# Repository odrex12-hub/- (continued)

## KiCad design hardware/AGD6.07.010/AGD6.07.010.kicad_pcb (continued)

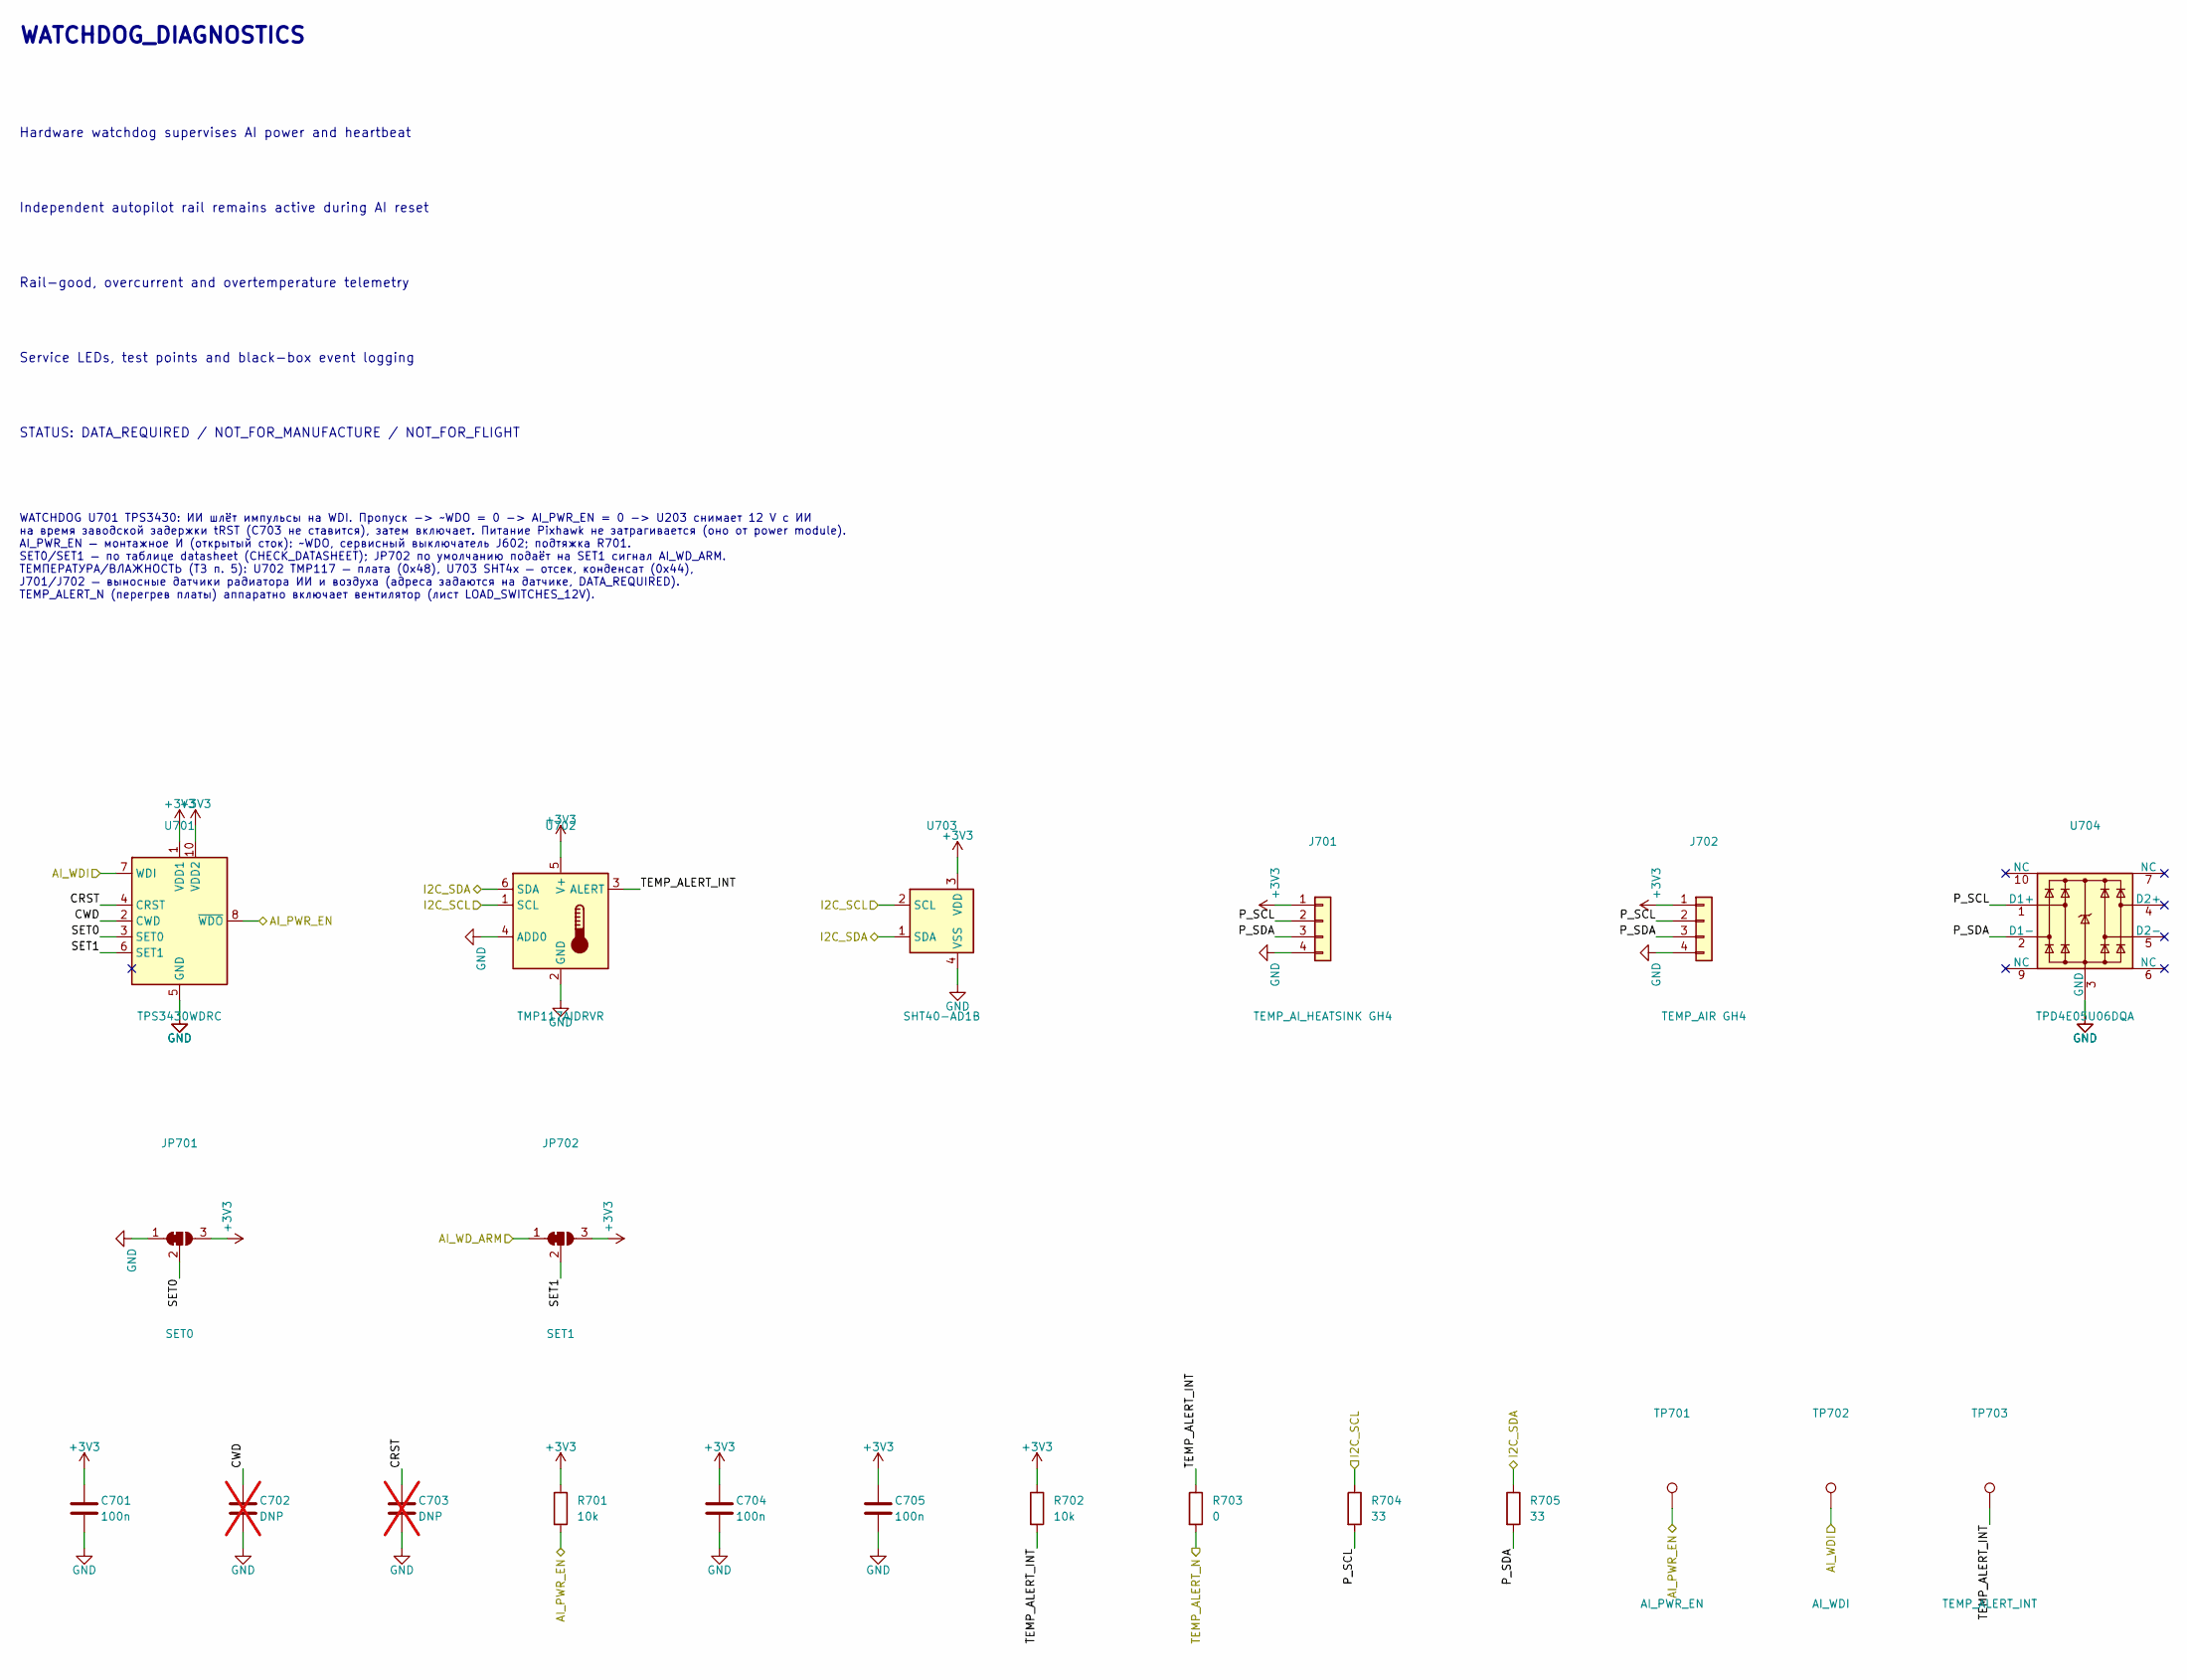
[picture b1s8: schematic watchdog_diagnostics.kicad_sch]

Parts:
C701, C704, C705: 100n; C_0402_1005Metric
C702, C703: DNP; C_0402_1005Metric; not fitted
J701: TEMP_AI_HEATSINK GH4; JST_GH_SM04B-GHS-TB_1x04-1MP_P1.25mm_Horizontal
J702: TEMP_AIR GH4; JST_GH_SM04B-GHS-TB_1x04-1MP_P1.25mm_Horizontal
JP701: SET0; SolderJumper-3_P1.3mm_Bridged12_RoundedPad1.0x1.5mm_NumberL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
JP702: SET1; SolderJumper-3_P1.3mm_Bridged12_RoundedPad1.0x1.5mm_NumberL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
R701, R702: 10k; R_0402_1005Metric
R703: 0; R_0402_1005Metric
R704, R705: 33; R_0402_1005Metric
TP701: AI_PWR_EN; TestPoint_Pad_D1.5mm
TP702: AI_WDI; TestPoint_Pad_D1.5mm
TP703: TEMP_ALERT_INT; TestPoint_Pad_D1.5mm
U701: TPS3430WDRC; VSON-10-1EP_3x3mm_P0.5mm_EP1.65x2.4mm
U702: TMP117AIDRVR; WSON-6-1EP_2x2mm_P0.65mm_EP1x1.6mm
U703: SHT40-AD1B; Sensirion_DFN-4_1.5x1.5mm_P0.8mm_SHT4x_NoCentralPad
U704: TPD4E05U06DQA; USON-10_2.5x1.0mm_P0.5mm

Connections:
+3V3: C701.1, C704.1, C705.1, J701.1, J702.1, JP701.3 (B), JP702.3 (B), R701.1, R702.1, U701.1 (VDD1), U701.10 (VDD2), U702.5 (V+), U703.3 (VDD); also elsewhere on the board
/AI_PWR_EN: R701.2, TP701.1, U701.8 (~WDO); also elsewhere on the board
/AI_WDI: TP702.1, U701.7 (WDI); also elsewhere on the board
/AI_WD_ARM: JP702.1 (A); also elsewhere on the board
/I2C_SCL: R704.1, U702.1 (SCL), U703.2 (SCL); also elsewhere on the board
/I2C_SDA: R705.1, U702.6 (SDA), U703.1 (SDA); also elsewhere on the board
/TEMP_ALERT_N: R703.2; also elsewhere on the board
/WATCHDOG_DIAGNOSTICS/CRST: C703.1, U701.4 (CRST)
/WATCHDOG_DIAGNOSTICS/CWD: C702.1, U701.2 (CWD)
/WATCHDOG_DIAGNOSTICS/P_SCL: J701.2, J702.2, R704.2, U704.1 (D1+)
/WATCHDOG_DIAGNOSTICS/P_SDA: J701.3, J702.3, R705.2, U704.2 (D1-)
/WATCHDOG_DIAGNOSTICS/SET0: JP701.2 (C), U701.3 (SET0)
/WATCHDOG_DIAGNOSTICS/SET1: JP702.2 (C), U701.6 (SET1)
/WATCHDOG_DIAGNOSTICS/TEMP_ALERT_INT: R702.2, R703.1, TP703.1, U702.3 (ALERT)
GND: C701.2, C702.2, C703.2, C704.2, C705.2, J701.4, J702.4, JP701.1 (A), U701.5 (GND), U701.11 (GND), U702.2 (GND), U702.4 (ADD0), U703.4 (VSS), U704.3 (GND), U704.8 (GND); also elsewhere on the board

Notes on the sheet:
Service LEDs, test points and black-box event logging
STATUS: DATA_REQUIRED / NOT_FOR_MANUFACTURE / NOT_FOR_FLIGHT
WATCHDOG_DIAGNOSTICS
Hardware watchdog supervises AI power and heartbeat
Rail-good, overcurrent and overtemperature telemetry
Independent autopilot rail remains active during AI reset
WATCHDOG U701 TPS3430: ИИ шлёт импульсы на WDI. Пропуск -> ~WDO = 0 -> AI_PWR_EN = 0 -> U203 снимает 12 V с ИИ на время заводской задержки tRST (C703 не ставится), затем включает. Питание Pixhawk не затрагивается (оно от power module). AI_PWR_EN — монтажное И (открытый сток): ~WDO, сервисный выключ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

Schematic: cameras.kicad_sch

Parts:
C901, C902: 10u 25V; C_1210_3225Metric
F901, F902: 1.1A; Fuse_1812_4532Metric
J901: CAM_FRONT_PWR XH2; JST_XH_B2B-XH-A_1x02_P2.50mm_Vertical
J902: CAM_DOWN_PWR XH2; JST_XH_B2B-XH-A_1x02_P2.50mm_Vertical

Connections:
+12V: F901.1, F902.1; also elsewhere on the board
/CAMERAS/V12_CAMD: C902.1, F902.2, J902.1
/CAMERAS/V12_CAMF: C901.1, F901.2, J901.1
GND: C901.2, C902.2, J901.2, J902.2; also elsewhere on the board

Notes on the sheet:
Protected power switching and synchronization trigger
CAMERAS
High-speed links routed away from switching power stages
Front navigation camera and downward observation camera
Optional depth/obstacle camera interface
DATA_REQUIRED: camera models, interface and cable type
КАМЕРЫ (ТЗ п. 4): питание 12 V через PTC. Видео: камера вперёд (SIYI A2 mini) — Ethernet через коммутатор, камера вниз — Ethernet кабелем напрямую в ИИ или в коммутатор SwitchBlox (лист ETHERNET). Синхронизация: CAM_TRIG (AUX7 Pixhawk) -> J806 на листе LOAD_SWITCHES_12V. Модели камер, объективы, ка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

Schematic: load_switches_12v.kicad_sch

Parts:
BZ801: 12V active buzzer; Buzzer_12x9.5RM7.6
C804, C811, C821, C831: 100n; C_0402_1005Metric
C805: 10u 25V; C_1210_3225Metric
D801, D802, D803, D804, D805, D808: SS14; D_SMA
D806, D809: ESD9B5.0ST5G; D_SOD-923
D807: BAT54C; SOT-23
D811, D812, D813: BAT54S; SOT-23
F801: 0.5A; Fuse_1206_3216Metric
F802: 1.5A; Fuse_1812_4532Metric
J801: VALVE1 XH2; JST_XH_B2B-XH-A_1x02_P2.50mm_Vertical
J802: VALVE2 XH2; JST_XH_B2B-XH-A_1x02_P2.50mm_Vertical
J803: LIGHTS XH2; JST_XH_B2B-XH-A_1x02_P2.50mm_Vertical
J804: FAN XH2; JST_XH_B2B-XH-A_1x02_P2.50mm_Vertical
J805: HEATER XH2; JST_XH_B2B-XH-A_1x02_P2.50mm_Vertical
J806: PUMP_PWM + CAM_TRIG GH4; JST_GH_SM04B-GHS-TB_1x04-1MP_P1.25mm_Horizontal
Q801, Q803, Q804: AO3400A; SOT-23
Q802: AO3401A; SOT-23
R804, R811, R821, R831: 4.7k; R_0402_1005Metric
R805, R842, R852, R872: 100k; R_0402_1005Metric
R806: 22k; R_0402_1005Metric
R807, R813, R823, R833: 10k; R_0402_1005Metric
R812, R822, R832: 470; R_0402_1005Metric
R841, R851, R861, R862, R871: 100; R_0402_1005Metric
TP801: ADC_RDY; TestPoint_Pad_D1.5mm
U801, U802, U803: BTS5030-1EJA; Infineon_PG-DSO-8-43
U804: ADS1115IDGSR; TSSOP-10_3x3mm_P0.5mm

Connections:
+3V3: C804.1, D811.2 (K), D812.2 (K), D813.2 (K), Q802.2 (S), R804.1, R807.1, U804.1 (ADDR), U804.8 (VDD); also elsewhere on the board
+12V: BZ801.1 (+), D808.1 (K); also elsewhere on the board
+12VA: C805.1, F801.1, F802.1, R805.1, U801.9 (VS), U802.9 (VS), U803.9 (VS); also elsewhere on the board
/BUZZER_CTL: R871.1; also elsewhere on the board
/CAM_TRIG: R862.1; also elsewhere on the board
/FAN_CTL: R841.1; also elsewhere on the board
/HEATER_CTL: R851.1; also elsewhere on the board
/I2C_SCL: U804.10 (SCL); also elsewhere on the board
/I2C_SDA: U804.9 (SDA); also elsewhere on the board
/LIGHTS_CTL: R831.1; also elsewhere on the board
/LOAD_SWITCHES_12V/ADC_RDY: R807.2, TP801.1, U804.2 (ALERT/RDY)
/LOAD_SWITCHES_12V/ALERT_DRV: D807.2, Q802.3 (D)
/LOAD_SWITCHES_12V/BUZ_G: Q804.1 (G), R871.2, R872.1
/LOAD_SWITCHES_12V/BUZ_N: BZ801.2 (-), D808.2 (A), Q804.3 (D)
/LOAD_SWITCHES_12V/DEN: R804.2, U801.3 (DEN), U802.3 (DEN), U803.3 (DEN)
/LOAD_SWITCHES_12V/FAN_CTL_R: D807.1, R841.2
/LOAD_SWITCHES_12V/FAN_G: D807.3, Q801.1 (G), R842.1
/LOAD_SWITCHES_12V/FAN_N: D804.2 (A), J804.2, Q801.3 (D)
/LOAD_SWITCHES_12V/HEAT_G: Q803.1 (G), R851.2, R852.1
/LOAD_SWITCHES_12V/HEAT_N: D805.2 (A), J805.2, Q803.3 (D)
/LOAD_SWITCHES_12V/IN1: R811.2, U801.2 (IN)
/LOAD_SWITCHES_12V/IN2: R821.2, U802.2 (IN)
/LOAD_SWITCHES_12V/IN3: R831.2, U803.2 (IN)
/LOAD_SWITCHES_12V/IS1: R812.1, R813.1, U801.4 (IS)
/LOAD_SWITCHES_12V/IS1_F: C811.1, D811.3 (COM), R813.2, U804.4 (AIN0)
/LOAD_SWITCHES_12V/IS2: R822.1, R823.1, U802.4 (IS)
/LOAD_SWITCHES_12V/IS2_F: C821.1, D812.3 (COM), R823.2, U804.5 (AIN1)
/LOAD_SWITCHES_12V/IS3: R832.1, R833.1, U803.4 (IS)
/LOAD_SWITCHES_12V/IS3_F: C831.1, D813.3 (COM), R833.2, U804.6 (AIN2)
/LOAD_SWITCHES_12V/OUT1: D801.1 (K), J801.1, U801.6 (OUT), U801.7 (OUT), U801.8 (OUT)
/LOAD_SWITCHES_12V/OUT2: D802.1 (K), J802.1, U802.6 (OUT), U802.7 (OUT), U802.8 (OUT)
/LOAD_SWITCHES_12V/OUT3: D803.1 (K), J803.1, U803.6 (OUT), U803.7 (OUT), U803.8 (OUT)
/LOAD_SWITCHES_12V/PUMP_C: D806.1 (A1), J806.1, R861.2
/LOAD_SWITCHES_12V/TRIG_C: D809.1 (A1), J806.2, R862.2
/LOAD_SWITCHES_12V/V12_FAN: D804.1 (K), F801.2, J804.1
/LOAD_SWITCHES_12V/V12_HEAT: D805.1 (K), F802.2, J805.1
/LOAD_SWITCHES_12V/V12_MON: R805.2, R806.1, U804.7 (AIN3)
/PUMP_PWM: R861.1; also elsewhere on the board
/TEMP_ALERT_N: Q802.1 (G); also elsewhere on the board
/VALVE1_CTL: R811.1; also elsewhere on the board
/VALVE2_CTL: R821.1; also elsewhere on the board
GND: C804.2, C805.2, C811.2, C821.2, C831.2, D801.2 (A), D802.2 (A), D803.2 (A), D806.2 (A2), D809.2 (A2), D811.1 (A), D812.1 (A), D813.1 (A), J801.2, J802.2, J803.2, J806.3, J806.4, Q801.2 (S), Q803.2 (S), Q804.2 (S), R806.2, R812.2, R822.2, R832.2, R842.2, R852.2, R872.2, U801.1 (GND), U802.1 (GND), U803.1 (GND), U804.3 (GND); also elsewhere on the board

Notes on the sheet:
LOAD_SWITCHES_12V
Ключи 12 V: 2 клапана, огни; вентилятор, нагреватель; сигнал насоса
ТРИ ЗАЩИЩЁННЫХ КЛЮЧА 12 V (ТЗ п. 1): U801/U802 — клапаны 1, 2; U803 — огни. BTS5030-1EJA: защита от КЗ и перегрева, диагностика обрыва/КЗ по току IS -> АЦП U804 ADS1115 (I2C 0x49) -> Pixhawk/ИИ. Обратные диоды SS14 на каждом выходе. Порог входа IN от 3.3 V логики Pixhawk и номинал R_IS — CHECK_DATA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

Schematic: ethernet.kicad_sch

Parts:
C1001: 10u 25V; C_1210_3225Metric
C1002: 100n; C_0402_1005Metric
F1001: 0.5A; Fuse_1206_3216Metric
J1001: SWITCHBLOX_PWR GH2; JST_GH_SM02B-GHS-TB_1x02-1MP_P1.25mm_Horizontal

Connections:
+12V: F1001.1; also elsewhere on the board
/ETHERNET/V12_ETH: C1001.1, C1002.1, F1001.2, J1001.1
GND: C1001.2, C1002.2, J1001.2; also elsewhere on the board

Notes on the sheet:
ETHERNET
Питание коммутатора BotBlox SwitchBlox (5 портов 10/100)
ETHERNET rev 0.4 (DECISIONS D15, D19): коммутатор — готовый модуль BotBlox SwitchBlox (5 портов 10/100 Мбит/с, неблокирующий, вход 5.1–60 V, 45 x 45 мм, разъёмы Molex PicoBlade, авто MDI-X; для дронов и Pixhawk). Сетевые кабели идут напрямую от устройств к SwitchBlox: 1 Pixhawk 6X ETH, 2 SIYI MK15,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

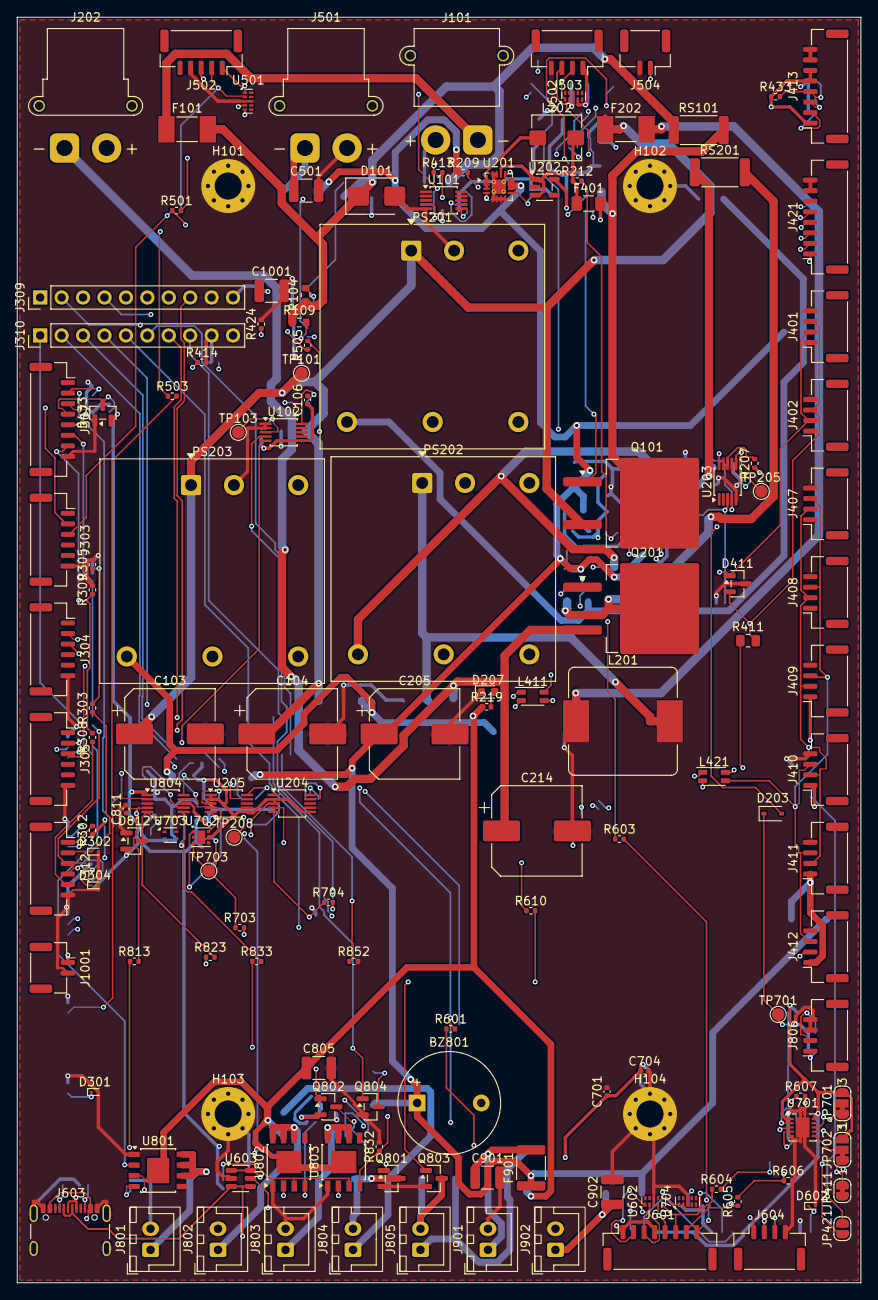
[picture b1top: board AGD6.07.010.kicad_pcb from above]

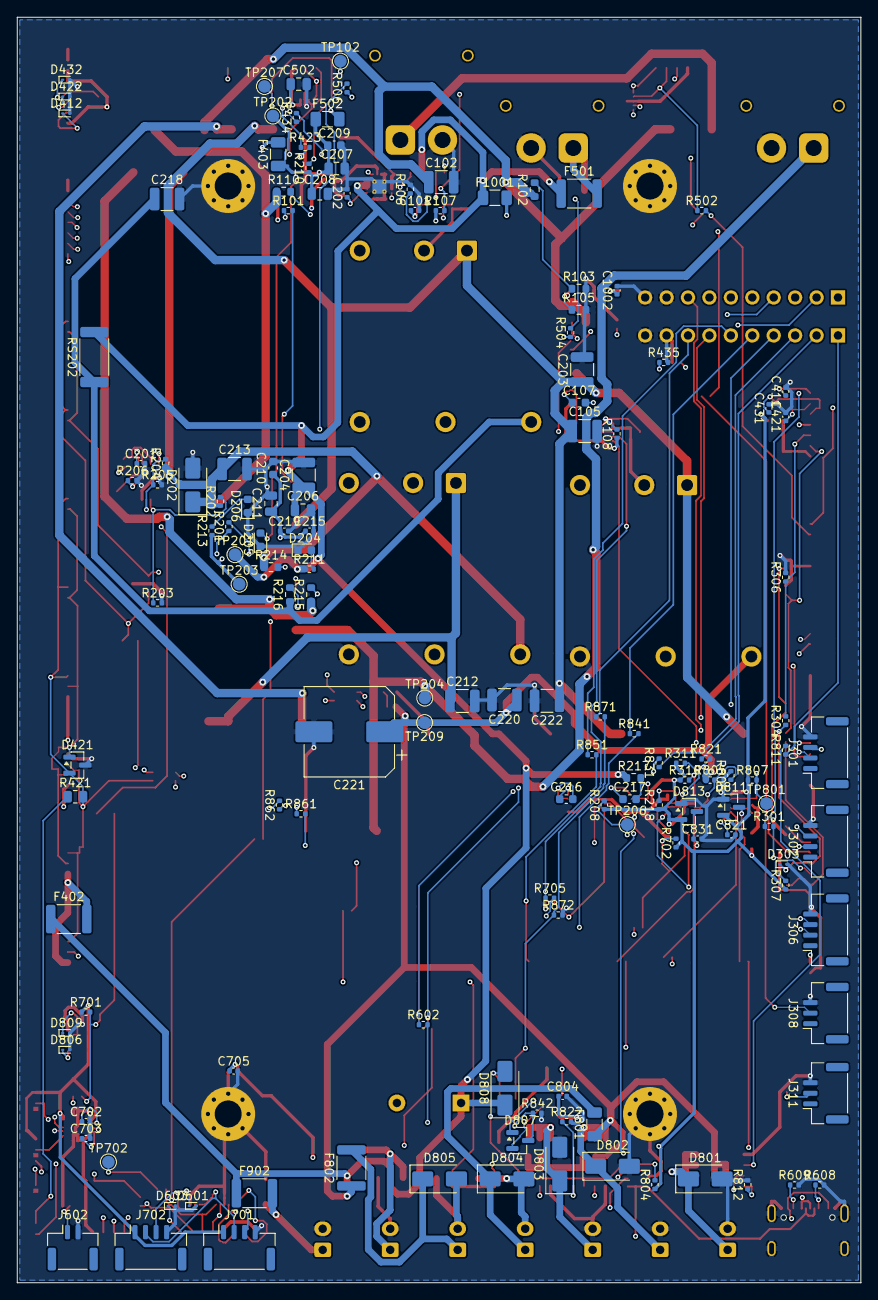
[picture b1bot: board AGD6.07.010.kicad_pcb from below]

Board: 4 copper layers, 100.0 x 150.0 mm, 286 parts (142 on the bottom side), 161 nets.

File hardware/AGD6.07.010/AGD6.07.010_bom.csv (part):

"Обозначение","Номинал","Корпус","Кол-во","Примечание","DNP"
"BZ801","12V active buzzer","Buzzer_Beeper:Buzzer_12x9.5RM7.6","1","",""
"C101","1u 16V X5R","Capacitor_SMD:C_0402_1005Metric","1","РАСЧЁТ: calculations.md",""
"C102,C105","1u 100V","Capacitor_SMD:C_1210_3225Metric","2","",""
"C103,C104","100u 100V","Capacitor_SMD:CP_Elec_10x10.5","2","",""
"C106,C215,C219,C411,C421,C701,C704,C705,C804,C811,C821,C831,C1002","100n","Capacitor_SMD:C_0402_1005Metric","13","",""
"C107","100n 100V","Capacitor_SMD:C_0603_1608Metric","1","",""
"C201","220n","Capacitor_SMD:C_0402_1005Metric","1","РАСЧЁТ: calculations.md",""
"C202","3.3n","Capacitor_SMD:C_0402_1005Metric","1","CHECK_DATASHEET",""
"C203,C222","4.7u 100V","Capacitor_SMD:C_1210_3225Metric","2","",""
"C204,C213,C218,C220","22u 25V","Capacitor_SMD:C_1210_3225Metric","4","",""
"C205,C214,C221","100u 25V","Capacitor_SMD:CP_Elec_10x10.5","3","",""
"C206","10u 25V","Capacitor_SMD:C_0805_2012Metric","1","",""
"C207,C208","22u 10V","Capacitor_SMD:C_0805_2012Metric","2","",""
"C209,C210","1u","Capacitor_SMD:C_0603_1608Metric","2","",""
"C211,C502","10u","Capacitor_SMD:C_0805_2012Metric","2","",""
"C212","10u 100V","Capacitor_SMD:C_1210_3225Metric","1","",""
"C216,C217","100n","Capacitor_SMD:C_0603_1608Metric","2","",""
"C431","1n","Capacitor_SMD:C_0402_1005Metric","1","",""
"C501,C805,C901,C902,C1001","10u 25V","Capacitor_SMD:C_1210_3225Metric","5","",""
"C702,C703","DNP","Capacitor_SMD:C_0402_1005Metric","2","РАСЧЁТ: calculations.md","DNP"
"D101","SM6T75A","Diode_SMD:D_SMB","1","CHECK_DATASHEET",""
"D202","SMAJ15A","Diode_SMD:D_SMA","1","CHECK_DATASHEET",""
"D203","BAT54WS","Diode_SMD:D_SOD-323","1","",""
"D204","12V","LED_SMD:LED_0603_1608Metric","1","",""
"D205","5V","LED_SMD:LED_0603_1608Metric","1","",""
"D206","3V3","LED_SMD:LED_0603_1608Metric","1","",""
"D207","12VA","LED_SMD:LED_0603_1608Metric","1","",""
"D301,D302,D303,D304,D412,D422,D432,D601,D602,D603,D806,D809","ESD9B5.0ST5G","Diode_SMD:D_SOD-923","12","",""
"D411,D421","NUP2105L","Package_TO_SOT_SMD:SOT-23","2","",""
"D433,D811,D812,D813","BAT54S","Package_TO_SOT_SMD:SOT-23","4","",""
"D801,D802,D803,D804,D805,D808","SS14","Diode_SMD:D_SMA","6","",""
"D807","BAT54C","Package_TO_SOT_SMD:SOT-23","1","",""
"F101","7A 60V Littelfuse 0456007","Fuse:Fuse_Littelfuse-NANO2-451_453","1","CHECK_DATASHEET",""
"F202","3A 60V Littelfuse 0456003","Fuse:Fuse_Littelfuse-NANO2-451_453","1","CHECK_DATASHEET",""
"F401,F502,F801,F1001","0.5A","Fuse:Fuse_1206_3216Metric","4","",""
"F402,F901,F902","1.1A","Fuse:Fuse_1812_4532Metric","3","",""
"F403","0.2A","Fuse:Fuse_1206_3216Metric","1","",""
"F501,F802","1.5A","Fuse:Fuse_1812_4532Metric","2","",""
"H101,H102,H103,H104","M3","MountingHole:MountingHole_3.2mm_M3_Pad_Via","4","",""
"J101","PDB_14S XT30","Connector_AMASS:AMASS_XT30PW-M_1x02_P2.50mm_Horizontal","1","",""
"J202","AI_POWER_12V XT30","Connector_AMASS:AMASS_XT30PW-F_1x02_P2.50mm_Horizontal","1","",""
"J301","PX_CAN1 GH4","Connector_JST:JST_GH_SM04B-GHS-TB_1x04-1MP_P1.25mm_Horizontal","1","",""
"J302","PX_CAN2 GH4","Connector_JST:JST_GH_SM04B-GHS-TB_1x04-1MP_P1.25mm_Horizontal","1","",""
"J303","PX_TELEM1 SIYI GH6","Connector_JST:JST_GH_SM06B-GHS-TB_1x06-1MP_P1.25mm_Horizontal","1","",""
"J304","PX_TELEM2 AI GH6","Connector_JST:JST_GH_SM06B-GHS-TB_1x06-1MP_P1.25mm_Horizontal","1","",""
"J305","PX_TELEM3 RADAR GH6","Connector_JST:JST_GH_SM06B-GHS-TB_1x06-1MP_P1.25mm_Horizontal","1","",""
"J306","PX_I2C GH4","Connector_JST:JST_GH_SM04B-GHS-TB_1x04-1MP_P1.25mm_Horizontal","1","",""
"J307","PX_AD&IO GH8","Connector_JST:JST_GH_SM08B-GHS-TB_1x08-1MP_P1.25mm_Horizontal","1","",""
"J308","PX_RC_IN GH3","Connector_JST:JST_GH_SM03B-GHS-TB_1x03-1MP_P1.25mm_Horizontal","1","",""
"J309","PX_MAIN 1-8","Connector_PinHeader_2.54mm:PinHeader_1x10_P2.54mm_Vertical","1","",""
"J310","PX_AUX 1-8","Connector_PinHeader_2.54mm:PinHeader_1x10_P2.54mm_Vertical","1","",""
"J311","FTS GH3","Connector_JST:JST_GH_SM03B-GHS-TB_1x03-1MP_P1.25mm_Horizontal","1","",""
"J312","MODE_SWITCH + LID/BATT_LATCH GH6","Connector_JST:JST_GH_SM06B-GHS-TB_1x06-1MP_P1.25mm_Horizontal","1","",""
"J401","CAN1 ESC CHAIN START GH4","Connector_JST:JST_GH_SM04B-GHS-TB_1x04-1MP_P1.25mm_Horizontal","1","",""
"J402","CAN1 ESC CHAIN RETURN GH4","Connector_JST:JST_GH_SM04B-GHS-TB_1x04-1MP_P1.25mm_Horizontal","1","",""
"J407","PM08-CAN GH4","Connector_JST:JST_GH_SM04B-GHS-TB_1x04-1MP_P1.25mm_Horizontal","1","",""
"J408","BMS CAN GH4","Connector_JST:JST_GH_SM04B-GHS-TB_1x04-1MP_P1.25mm_Horizontal","1","",""
"J409","REMOTE_ID GH4","Connector_JST:JST_GH_SM04B-GHS-TB_1x04-1MP_P1.25mm_Horizontal","1","",""
"J410","GNSS2 (резерв) GH4","Connector_JST:JST_GH_SM04B-GHS-TB_1x04-1MP_P1.25mm_Horizontal","1","",""
"J411","OBSTACLE_1 GH4","Connector_JST:JST_GH_SM04B-GHS-TB_1x04-1MP_P1.25mm_Horizontal","1","",""
"J412","OBSTACLE_2 GH4","Connector_JST:JST_GH_SM04B-GHS-TB_1x04-1MP_P1.25mm_Horizontal","1","",""
"J413","SPRAY_SENSORS GH8 (давл./уровень/расход)","Connector_JST:JST_GH_SM08B-GHS-TB_1x08-1MP_P1.25mm_Horizontal","1","",""
"J421","ESC1-6 PWM backup GH8","Connector_JST:JST_GH_SM08B-GHS-TB_1x08-1MP_P1.25mm_Horizontal","1","",""
"J501","SIYI_PWR XT30","Connector_AMASS:AMASS_XT30PW-F_1x02_P2.50mm_Horizontal","1","",""
"J502","SIYI_DATA GH5","Connector_JST:JST_GH_SM05B-GHS-TB_1x05-1MP_P1.25mm_Horizontal","1","",""
"J503","RADAR_US-D1 GH4","Connector_JST:JST_GH_SM04B-GHS-TB_1x04-1MP_P1.25mm_Horizontal","1","",""
"J504","GNSS_PPS GH2","Connector_JST:JST_GH_SM02B-GHS-TB_1x02-1MP_P1.25mm_Horizontal","1","",""
"J601","AI_SIGNALS GH8","Connector_JST:JST_GH_SM08B-GHS-TB_1x08-1MP_P1.25mm_Horizontal","1","",""
"J602","AI_OFF_SWITCH GH2","Connector_JST:JST_GH_SM02B-GHS-TB_1x02-1MP_P1.25mm_Horizontal","1","",""
"J603","SERVICE USB-C","Connector_USB:USB_C_Receptacle_GCT_USB4105-xx-A_16P_TopMnt_Horizontal","1","",""
"J604","AI_USB GH4","Connector_JST:JST_GH_SM04B-GHS-TB_1x04-1MP_P1.25mm_Horizontal","1","",""
"J701","TEMP_AI_HEATSINK GH4","Connector_JST:JST_GH_SM04B-GHS-TB_1x04-1MP_P1.25mm_Horizontal","1","",""
"J702","TEMP_AIR GH4","Connector_JST:JST_GH_SM04B-GHS-TB_1x04-1MP_P1.25mm_Horizontal","1","",""
"J801","VALVE1 XH2","Connector_JST:JST_XH_B2B-XH-A_1x02_P2.50mm_Vertical","1","",""
"J802","VALVE2 XH2","Connector_JST:JST_XH_B2B-XH-A_1x02_P2.50mm_Vertical","1","",""
"J803","LIGHTS XH2","Connector_JST:JST_XH_B2B-XH-A_1x02_P2.50mm_Vertical","1","",""
"J804","FAN XH2","Connector_JST:JST_XH_B2B-XH-A_1x02_P2.50mm_Vertical","1","",""
"J805","HEATER XH2","Connector_JST:JST_XH_B2B-XH-A_1x02_P2.50mm_Vertical","1","",""
"J806","PUMP_PWM + CAM_TRIG GH4","Connector_JST:JST_GH_SM04B-GHS-TB_1x04-1MP_P1.25mm_Horizontal","1","",""
"J901","CAM_FRONT_PWR XH2","Connector_JST:JST_XH_B2B-XH-A_1x02_P2.50mm_Vertical","1","",""
"J902","CAM_DOWN_PWR XH2","Connector_JST:JST_XH_B2B-XH-A_1x02_P2.50mm_Vertical","1","",""
"J1001","SWITCHBLOX_PWR GH2","Connector_JST:JST_GH_SM02B-GHS-TB_1x02-1MP_P1.25mm_Horizontal","1","",""
"JP411","TERM_CAN1 (замкнута)","Jumper:SolderJumper-2_P1.3mm_Bridged_RoundedPad1.0x1.5mm","1","",""
"JP421","TERM_CAN2","Jumper:SolderJumper-2_P1.3mm_Open_RoundedPad1.0x1.5mm","1","",""
"JP701","SET0","Jumper:SolderJumper-3_P1.3mm_Bridged12_RoundedPad1.0x1.5mm_NumberLabels","1","CHECK_DATASHEET",""
"JP702","SET1","Jumper:SolderJumper-3_P1.3mm_Bridged12_RoundedPad1.0x1.5mm_NumberLabels","1","CHECK_DATASHEET",""
"L201","4.7u 5A","Inductor_SMD:L_Bourns_SRP1245A","1","CHECK_DATASHEET",""
"L202","2.2u 4A","Inductor_SMD:L_Bourns_SRP5030T","1","CHECK_DATASHEET",""
"L411,L421","744232090","Inductor_SMD:L_CommonMode_Wurth_WE-CNSW-1206","2","",""
"PS201,PS202,PS203","TRACO THL 40-4812WI","Converter_DCDC:Converter_DCDC_TRACO_THL40-xxxxWI_THT","3","",""
"Q101","100V N-MOSFET >=40A D2PAK (напр. IPB180N10S4-02)","Package_TO_SOT_SMD:TO-263-2","1","CHECK_DATASHEET",""
"Q201","40V N-MOSFET >=40A D2PAK (напр. IPB017N06N3)","Package_TO_SOT_SMD:TO-263-2","1","CHECK_DATASHEET",""
"Q801,Q803,Q804","AO3400A","Package_TO_SOT_SMD:SOT-23","3","",""
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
